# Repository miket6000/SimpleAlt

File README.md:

# SimpleAlt

A simple barometer based peak and logging altimeter for model rocketry with USB C charging and data transfer.  

## Technical details

SimpleAlt uses a Bosch BMP280 to measure the barometric altitude of the altimeter. When recording is started by pressing the button it takes a reference measurement which it calls "ground altitude". This is subtracted from the maximum altitude used in displaying the altitude achieved, however the raw barometric altitude is what is recorded onto the flash.  

The micro controller is an STM32F042, chosen for it's small physical size and built in USB peripheral.  

The flash chip is a Windbond W26Q16 which provides 16Mb (2MB) of recording. The current configuration of 5 bytes per sample (a 1 byte label and 32bit altitude) at 50Hz sample rate (this will probably be reduced to 25Hz in the future) provides a bit over 2hrs of continuous recording.  

The 30mAh battery will last approximately 3-4 hours in idle or recording mode, and about 24 hours in sleep mode, hough work is being done to extend this as the micro controller is not currently achieving the expected current draw. The shutdown mode will last approximately forever, however there is a strange bug in the current hardware revision whereby putting the STNS01 into shutdown mode does not fully succeed until the button is released and pressed again to put a load on the LDO. The cause of this is currently unknown.  

Charging, battery protection and the LDO are all supplied by the STNS01.  

## Using SimpleAlt

SimpleAlt has a simple user interface consisting of a single button and a single green LED (marked 's', for status). This allows it to be as light as possible but may take some getting used to.  

To show how this works this document describes LED flashes between angled brackets <>. A number between the brackets indicates the number of times the LED will flash. A '.' indicates a short pause and a '-' indicates a long pause. e.g.  
< 9 . 10 . 6 - >  
indicates 9 flashes, a short pause, 10 flashes, a short pause and then 6 flashes followed by a long pause. Most flashing sequences will repeat, the exception being the Button mode.  

### The Button
All operations are performed with a single press of the button. To change which options you want you simply hold the button down longer. The options available are:  
1. Wake from Sleep - If the SimpleAlt is in sleep mode, a quick press of the button will wake it up into Idle mode.  
2. Start/Stop recording - A slightly longer press on the button, until you see the first flash on the green LED < 1 >, will start or stop recording.  
3. Enter Sleep mode - holding the button for longer will result in a double flash of the LED after the first flash < 1 . 2 >. Releasing the button now will cause the SimpleAlt to go into sleep mode.  
4. Enter Shutdown mode - holding the button for longer still will result in a triple flash after the double flash < 1 . 2 . 3 >. Releasing the button now will result in the SimpleAlt going into Shutdown mode. The only way to wake SimpleAlt from Shutdown mode is to plug a power supply into the USB connector.  

Thats it! 

### The Green LED

< 1 - >     Idle mode  
< 1 . 2 . > Recording mode  
  
The LED is used to provide status and instant altitude information. Depending on the state of the SimpleAlt it will be displaying one of the below bits of information:
1. Idle mode - a single flash repeating < 1 - >.  
2. Recording mode - the led will alternate between 1 flash and 2 flashes with a short delay between them < 1 . 2 . >.  
3. Button mode - while holding down the button the led will flash once, then twice, then three times to indicate when to release to achieve different functions as described in the button section.  
4. Altitude mode - After exiting recording mode, so long as there was an altitude gain of at least 1m, the led will flash out the maximum altitude in metres. The number of flashes indicates the digit for each place in the number. Leading zero's are not flashed out, and a zero is otherwise flashed out as 10 flashes. So for example if your rocket got to 207m the SimpleAlt will flash < 2 . 10 . 7 - > and then repeat.  

### Charging

Plugging the SimpleAlt into a USB C power supply will result in it charging the battery. While charging the red LED will illuminate. When the battery is full the red LED will turn off. If a fault occured during charging (e.g. the battery voltage never rises high enough) the red LED will flash. This indicates a fault with the hardware or battery and will need to be repaired.  

### Putting it all together

A day flying might look like the following.  

Charge the SimpleAlt by plugging it in. When the red LED turns off, it's charged so unplug it and put it into Sleep mode by holding down the button until you see the double flash.  

Get to the flying field and get set up. When the rocket is ready to launch a quick press on the button wakes up the SimpleAlt and it starts slowly flashing that it's in Idle mode. Holding the button until the first flash puts the SimpleAlt into recording mode (and also sets the ground level), it starts flashing < 1 . 2 . 1 . 2 > put it into the payload bay and launch your rocket.  

On recovery of your rocket press the button until the green LED gives a single flash < 1 > and release to stop recording. The SimpleAlt will now flash out the altitude your rocket achieved in metres.  

Hold the button until the double flash to put the altimeter back into sleep mode, or load it straight into the next rocket and start recording again.  

Back at a computer use the plug the SimpleAlt into your computer using a USB C cable and use the Simple application to download your flights. The flights are added onto the list in order that they occured and the application also gives you the duration of the flight (from starting to stopping the recording) to help you find the right flights to download. For more details see the app guide.

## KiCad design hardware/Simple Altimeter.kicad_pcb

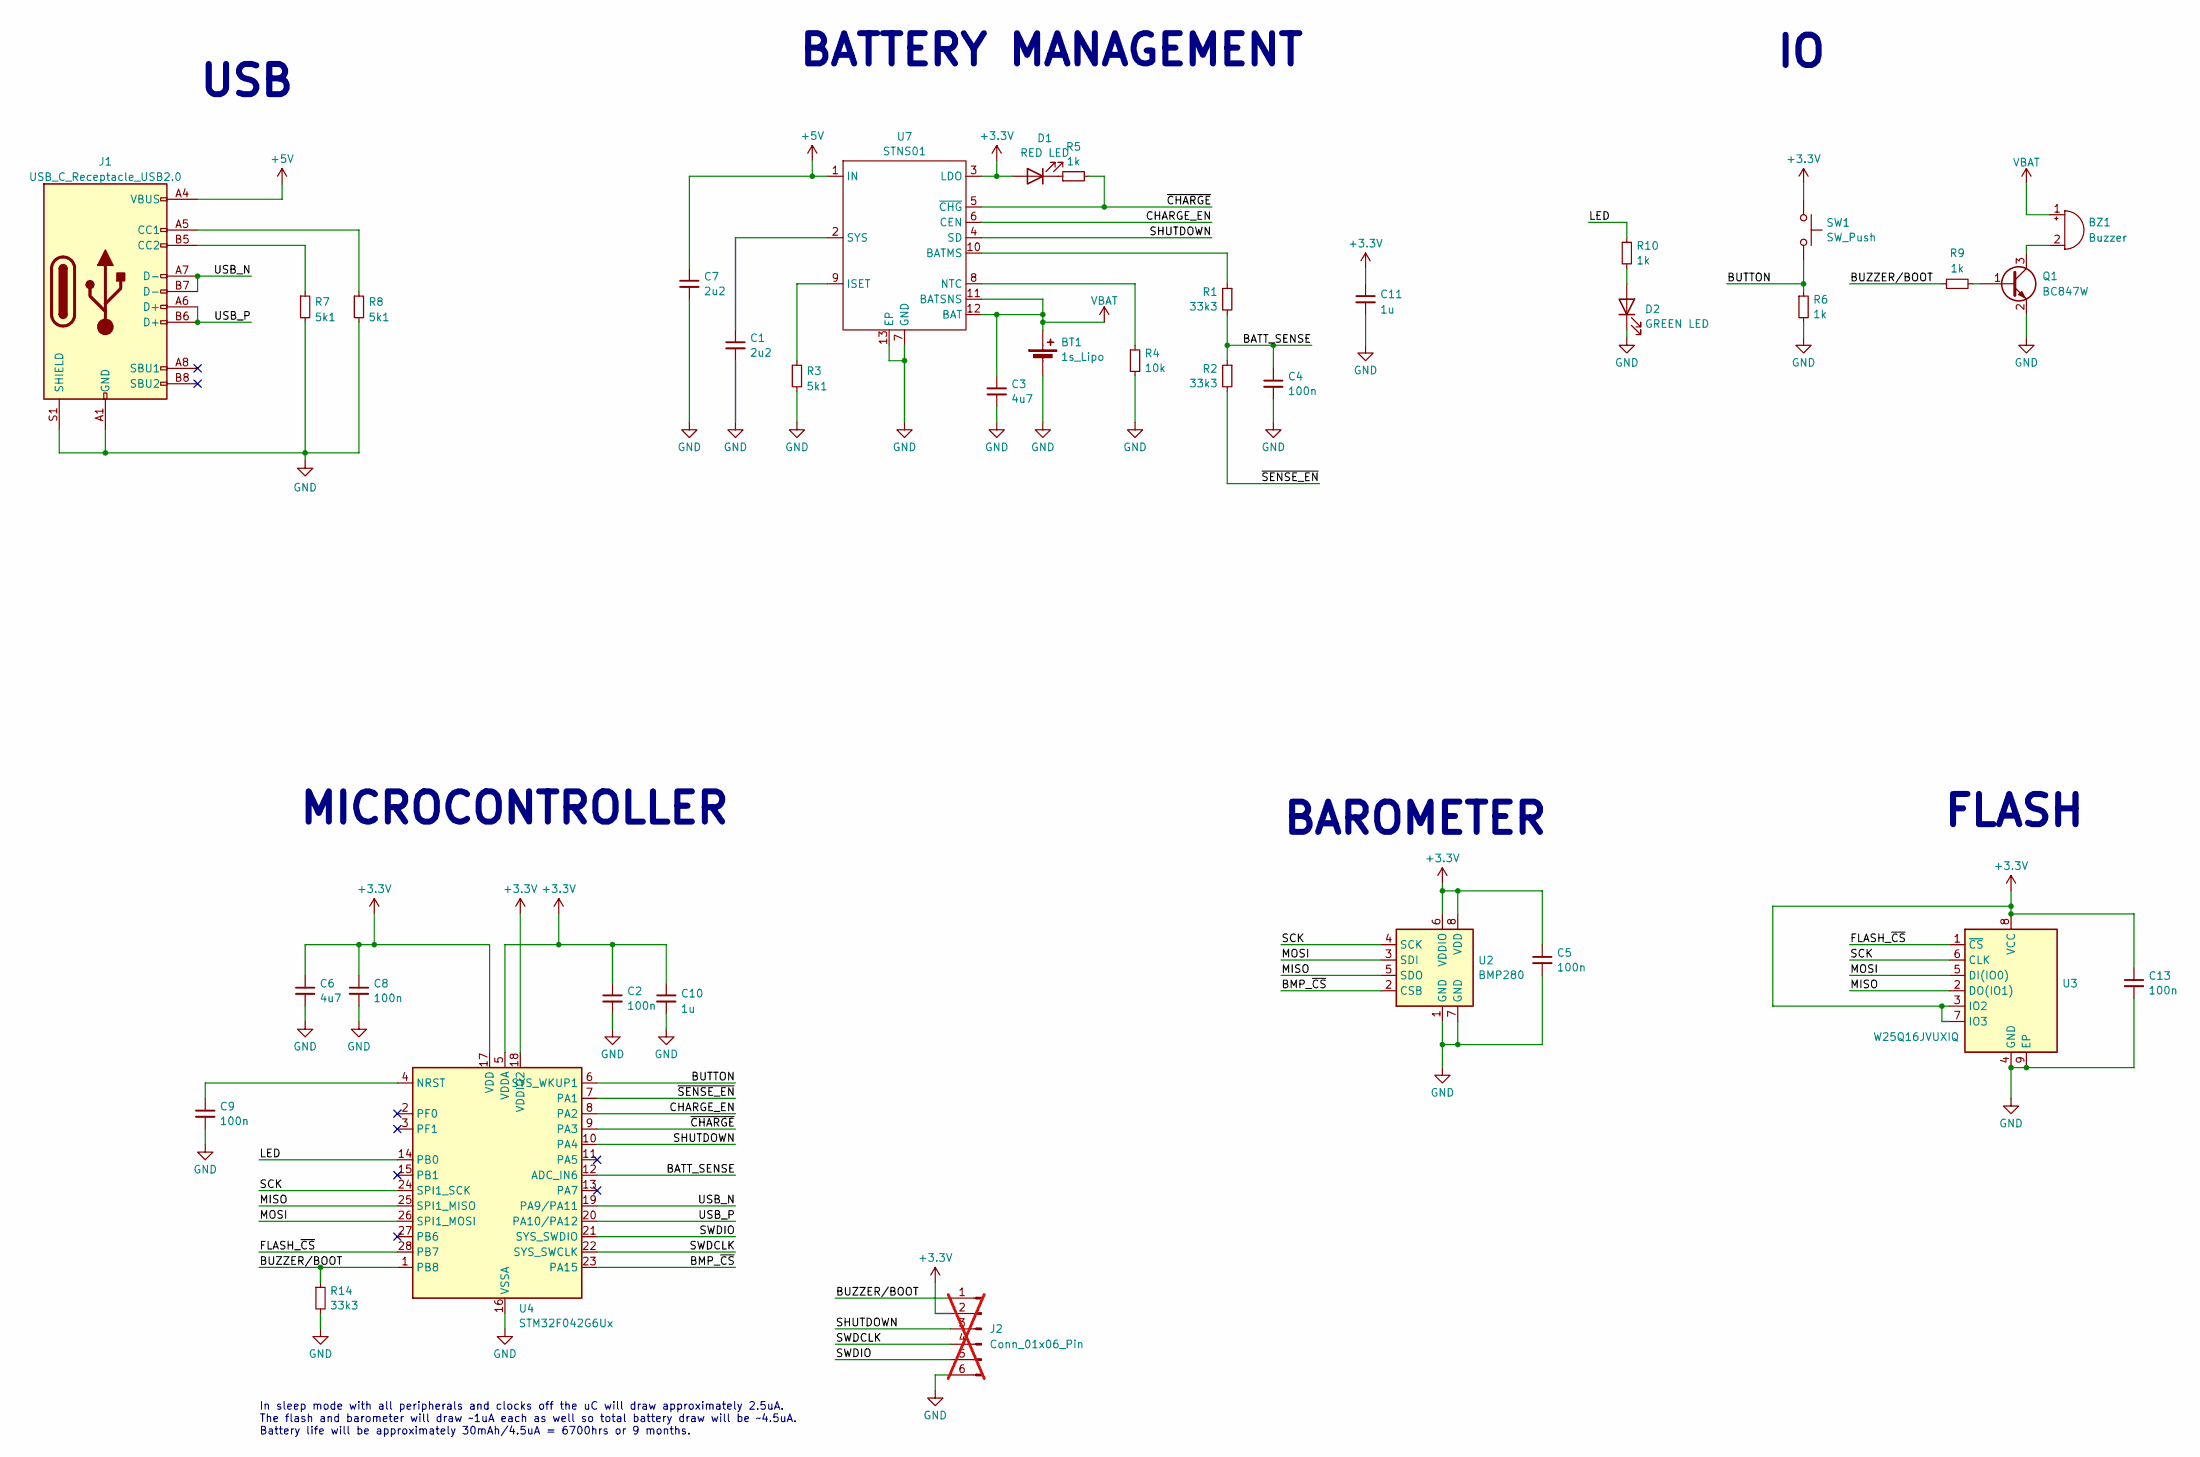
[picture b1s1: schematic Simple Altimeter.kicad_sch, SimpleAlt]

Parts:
BT1: 1s_Lipo; Lipo 401010
BZ1: Buzzer; Buzzer_0502
C1, C7: 2u2; C_0402_1005Metric; JLC Part Number C15849
C2, C4, C5, C8, C9, C13: 100n; C_0402_1005Metric
C3, C6: 4u7; C_0402_1005Metric; JLC Part Number C15849
C10, C11: 1u; C_0402_1005Metric; JLC Part Number C15849
D1: RED LED; LED_0603_1608Metric
D2: GREEN LED; LED_0603_1608Metric
J1: USB_C_Receptacle_USB2.0; USB_C_Receptacle_Palconn_UTC16-G; JLC Part Number C2831450
J2: Conn_01x06_Pin; PinHeader_1x06_P1.27mm_Vertical; not fitted
Q1: BC847W; SOT-323_SC-70
R1, R2, R14: 33k3; R_0402_1005Metric; JLC Part Number C3013567
R3, R7, R8: 5k1; R_0402_1005Metric; JLC Part Number C3013567
R4: 10k; R_0402_1005Metric; JLC Part Number C3013567
R5, R6, R10: 1k; R_0402_1005Metric; JLC Part Number C3013567
R9: 1k; R_0402_1005Metric
SW1: SW_Push; SW_SPST_B3U-1000P
U2: BMP280; Bosch_LGA-8_2x2.5mm_P0.65mm_ClockwisePinNumbering
U3: W25Q16JVUXIQ; Winbond_USON_8_EP_2x3mm
U4: STM32F042G6Ux; QFN-28_4x4mm_P0.5mm
U7: STNS01; DFN-12-1EP_3x3mm_P0.45mm_EP1.65x2.38mm

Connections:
+3.3V: C2.1, C5.1, C6.1, C8.1, C10.1, C11.1, C13.1, D1.2 (A), J2.2, SW1.2, U2.6 (VDDIO), U2.8 (VDD), U3.3 (IO2), U3.7 (IO3), U3.8 (VCC), U4.5 (VDDA), U4.17 (VDD), U4.18 (VDDIO2), U7.3 (LDO)
+5V: C7.1, J1.A4 (VBUS), J1.A9 (VBUS), J1.B4 (VBUS), J1.B9 (VBUS), U7.1 (IN)
/BATT_SENSE: C4.1, R1.2, R2.1, U4.12 (ADC_IN6)
/BMP_~CS: U2.2 (CSB), U4.23 (PA15)
/BUTTON: R6.1, SW1.1, U4.6 (SYS_WKUP1)
/BUZZER/BOOT: J2.1, R9.1, R14.1, U4.1 (PB8)
/CHARGE_EN: U4.8 (PA2), U7.6 (CEN)
/FLASH_~CS: U3.1 (~CS), U4.28 (PB7)
/LED: R10.1, U4.14 (PB0)
/MISO: U2.5 (SDO), U3.2 (DO(IO1)), U4.25 (SPI1_MISO)
/MOSI: U2.3 (SDI), U3.5 (DI(IO0)), U4.26 (SPI1_MOSI)
/SCK: U2.4 (SCK), U3.6 (CLK), U4.24 (SPI1_SCK)
/SHUTDOWN: J2.3, U4.10 (PA4), U7.4 (SD)
/SWDCLK: J2.4, U4.22 (SYS_SWCLK)
/SWDIO: J2.5, U4.21 (SYS_SWDIO)
/USB_N: J1.A7 (D-), J1.B7 (D-), U4.19 (PA9/PA11)
/USB_P: J1.A6 (D+), J1.B6 (D+), U4.20 (PA10/PA12)
/~CHARGE: R5.2, U4.9 (PA3), U7.5 (~CHG)
/~SENSE_EN: R2.2, U4.7 (PA1)
GND: BT1.2 (-), C1.2, C2.2, C3.2, C4.2, C5.2, C6.2, C7.2, C8.2, C9.2, C10.2, C11.2, C13.2, D2.1 (K), J1.A1 (GND), J1.A12 (GND), J1.B1 (GND), J1.B12 (GND), J1.S1 (SHIELD), J2.6, Q1.2 (E), R3.2, R4.2, R6.2, R7.2, R8.2, R14.2, U2.1 (GND), U2.7 (GND), U3.4 (GND), U3.9 (EP), U4.16 (VSSA), U7.7 (GND), U7.13 (EP)
unnamed: BZ1.2 (-), Q1.3 (C)
unnamed: D1.1 (K), R5.1
unnamed: D2.2 (A), R10.2
unnamed: J1.A5 (CC1), R8.1
unnamed: J1.B5 (CC2), R7.1
unnamed: Q1.1 (B), R9.2
unnamed: C9.1, U4.4 (NRST)
unnamed: R1.1, U7.10 (BATMS)
unnamed: R3.1, U7.9 (ISET)
unnamed: R4.1, U7.8 (NTC)
unnamed: C1.1, U7.2 (SYS)
VBAT: BT1.1 (+), BZ1.1 (+), C3.1, U7.11 (BATSNS), U7.12 (BAT)

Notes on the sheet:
FLASH
BAROMETER
MICROCONTROLLER
USB
In sleep mode with all peripherals and clocks off the uC will draw approximately 2.5uA. The flash and barometer will draw ~1uA each as well so total battery draw will be ~4.5uA. Battery life will be approximately 30mAh/4.5uA = 6700hrs or 9 months.
BATTERY MANAGEMENT

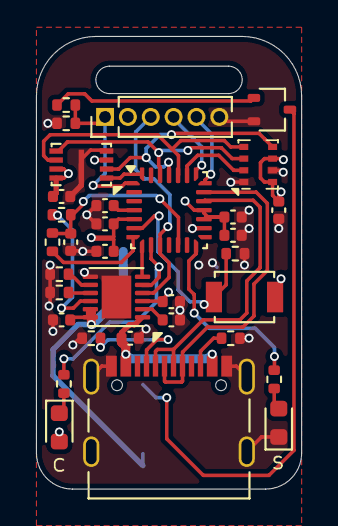
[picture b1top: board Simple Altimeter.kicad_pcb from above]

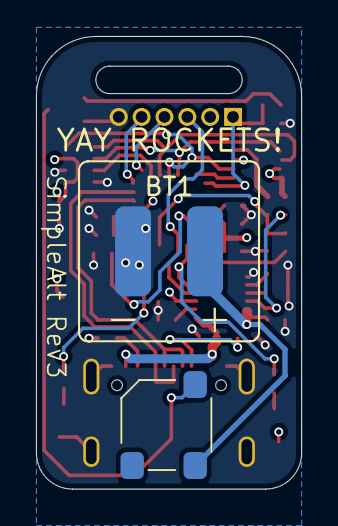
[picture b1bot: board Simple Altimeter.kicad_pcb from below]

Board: 4 copper layers, 14.7 x 25.1 mm, 35 parts (2 on the bottom side), 32 nets.

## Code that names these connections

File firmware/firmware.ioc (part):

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Mcu.Name=STM32F042G(4-6)Ux
Mcu.Package=UFQFPN28
Mcu.UserName=STM32F042G6Ux
PA0.GPIOParameters=GPIO_Label
PA0.GPIO_Label=BUTTON
PA0.Mode=SYS_WakeUp0
PA0.Signal=SYS_WKUP1
PA1.GPIOParameters=PinState,GPIO_Label
PA1.GPIO_Label=nSENSE_EN
PA1.PinState=GPIO_PIN_SET
PA1.Signal=GPIO_Output
PA11.Mode=Device
PA11.Signal=USB_DM
PA12.Mode=Device
PA12.Signal=USB_DP
PA13.Mode=Serial_Wire
PA13.Signal=SYS_SWDIO
PA14.Mode=Serial_Wire
PA14.Signal=SYS_SWCLK
PA15.GPIOParameters=PinState,GPIO_PuPd,GPIO_Label
PA15.GPIO_Label=BMP_CS
PA15.GPIO_PuPd=GPIO_PULLUP
PA15.PinState=GPIO_PIN_SET
PA15.Signal=GPIO_Output
PA2.GPIOParameters=PinState,GPIO_Label
PA2.GPIO_Label=CHARGE_EN
PA2.PinState=GPIO_PIN_SET
PA2.Signal=GPIO_Output
PA3.GPIOParameters=GPIO_PuPd,GPIO_Label
PA3.GPIO_Label=nCHARGE
PA3.GPIO_PuPd=GPIO_PULLUP
PA3.Signal=GPIO_Input
PA4.GPIOParameters=PinState,GPIO_PuPd,GPIO_Label
PA4.GPIO_Label=SHUTDOWN
PA4.GPIO_PuPd=GPIO_PULLDOWN
PA4.PinState=GPIO_PIN_RESET
PA4.Signal=GPIO_Output
PA6.GPIOParameters=GPIO_Label
PA6.GPIO_Label=BATT_SENSE
PA6.Mode=IN6
PA6.Signal=ADC_IN6
PB0.GPIOParameters=PinState,GPIO_Label
PB0.GPIO_Label=LED
PB0.PinState=GPIO_PIN_RESET
PB0.Signal=GPIO_Output
PB3.Mode=Full_Duplex_Master
PB3.Signal=SPI1_SCK
PB4.Mode=Full_Duplex_Master
PB4.Signal=SPI1_MISO
PB5.Mode=Full_Duplex_Master
PB5.Signal=SPI1_MOSI
PB7.GPIOParameters=PinState,GPIO_PuPd,GPIO_Label
PB7.GPIO_Label=FLASH_CS
PB7.GPIO_PuPd=GPIO_PULLUP
PB7.PinState=GPIO_PIN_SET
PB7.Signal=GPIO_Output
RCC.SYSCLKFreq_VALUE=48000000
RCC.SYSCLKSource=RCC_SYSCLKSOURCE_HSI48
board=custom

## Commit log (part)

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2024-06-22 Initial Commit
    Contains draft version of Kicad project files and production outputs. Also includes PDF schematic in docs folder.
2024-06-22 Added 3d render
2024-06-22 Added some of the critical datasheets.
2024-06-22 Fixed boot pin and strengthened teather loop. Added BOMs and manufacturing data.
2024-06-22 Corrected Q1 schematic symbol (was NMOS, now correctly showing PMOS)
2024-06-22 Corrected Q2 part number.
2024-06-22 updated button part number
2024-06-23 Adding operation.md
2024-06-24 Initial commit of STNS01 fork. This will probably become main at some stage in the future.
2024-06-24 Added power off method for debug, and updated operation.md for new hardware. Cleaned up production files.
2024-06-24 fixed footprint for W25Q16JVU
2024-06-26 Adding autogenerated firmware from CubeMX with hardware peripherals configured.
2024-06-26 Updated component 3d models and regenerated render.
2024-07-12 add blinky app with basic power management and button behaviour beware, it's an ugly proof of hardware, not 'real' code.
2024-07-12 Fixed button standby feature. Hold button for >2 seconds to sleep, >5 seconds to shutdown.
2024-07-13 Add a workflow to check compilation.
2024-07-13 Update workflow to use ubuntu
2024-07-13 Ignore build files and add make recipie to program board
2024-07-13 fix white space in Makefile
2024-07-15 Changed USB device from Mass Storage to CDC and added dummy transmitter to main loop. Also added DMA for SPI, not currently configured.
2024-07-16 Added demo of led blink sequence engine functionality. Need to add function to modify blink_queue.
2024-07-16 changed 'queue' to 'sequence' in variable names and added a short pause
2024-07-16 Added capability to define the sequence outside of led.c
2024-07-19 updated LED sequence engine
2024-07-20 Add some makefile targets for setup and debugging
2024-07-20 cleaning up coding convention (moving towards 'C Coding Standard') and moved power management into it's own file.
2024-07-21 Added driver and demo for the bmp280. USB prints out voltage, temperature and pressure.
2024-07-24 Added tool to precalculate pressure to altitude lookup table and implemented function to calculate and report altitude.
2024-07-27 adding test & interative terminal
2024-07-27 added parameter capability to command interpreter and added ground level subtraction capability.
2024-07-28 fixed write enable function in w25q.c added a raw register read function to the command interpreter, and cleaned up some global variables.
2024-07-28 fixed error where a delay in the USB receive routine would cause USB to crash. Fix was to simplify USB receive routine to a single memcpy.
2024-07-28 cleaning up temporary files and provided .gitignore
2024-07-28 basic working flash using w25qxx library.
2024-07-29 working recording to flash by using the button to toggle 'record' mode.
2024-07-29 added simple app to get logs from altimeter and create csv file
2024-07-30 fixed unsigned int error in altitude calculation
2024-07-30 fixed previous fix (didn't remove a function that relied on gruond level function) and improved power on button logic.
2024-07-30 Added binary download of data and updated python app to improve read speeds and actually create the csv file.
2024-07-31 Update simple.py to make altitude signed integer.
2024-07-31 Update simple.py to correct csv line endings
2024-07-31 index on main: d039ded Added binary download of data and updated python app to improve read speeds and actually create the csv file.
2024-07-31 Updated app to allow user to select which of the detected flights to download and added first successful launch plot to docs
2024-07-31 fixed csv titles
2024-08-02 Improvements to shutdown code, increased maximum pressure capability, added led_add_number_sequence() capbility and changed logging to relative altitude instead of absolute.
2024-08-03 Fixed led altitude flashing
2024-08-06 added c version of application
2024-08-06 removed build artifact
2024-08-07 pulled out button code into a seperate file, added a more traditional state machine to main loop and updated button logic to indicate how long to hold the button.
2024-08-07 updated README with technical overview and usage isntructions.
2024-08-07 Update README.md
    Fixed markdown formatting errors.
2024-08-10 made significant improvements to data transfere speed (USB buffer read/write shouldn't have been in the systick gated code)
2024-08-10 Added basic flutter based UI. Only tested on Linux.
2024-08-12 added binary dump to app/c and improved axis title readability in app/flutter.
2024-08-13 fixed state transition from recording to SLEEP or SHUTDOWN causing loss of data.
2024-08-14 Added app screenshot to docs.
2024-08-14 fixed initalization error in idle timeout counter
2024-08-14 updated readme with render and app screenshot
2024-08-14 changed filename for screenshot
2024-08-14 fixed very annoying problem where the flash chip was put to sleep but not woken up on power up, causing issues reading from and writing to it.
2024-08-18 tidied up flutter app, improved chart tooltip and added save capabilities.
2024-08-18 minor refactoring
2024-08-25 added flash dump capability to c app.
2024-08-26 moderate refactor of power and filesystem code to improve modularity
2024-08-26 Added bounds checking to flash writes to prevent overrunning the available flash space and corrupting the filesystem.
2024-08-28 fixed error with serial port not being correctly configured and binary dump reading too many bytes.
2024-08-31 Make C app build on FreeBSD 14.1
2024-08-31 Add C app build to workflow
2024-08-31 Run workflow every push or pull request
2024-08-31 Switch buffers to use void* rather than uint8_t*
    void * is a pointer to anything which is what you probably want here.
    It also avoids the cast when calling but may require casting in the function.
    also trailing white space has been removed.
2024-08-31 Add additional data items to each record.
2024-08-31 Make all warnings treated as errors
2024-09-01 First pass at pulling multiple records out of the flash
2024-09-01 WIP: begin updating the dart to handle multiple records types
2024-09-04 added configuration capability and reduced heap size to 0 to free up RAM
2024-09-04 changed fs_save data type to void *, and added other variables to log.
2024-09-05 Updated timing system to make functions largely tick length agnostic. Added ability to log variables at differnt rates. Improved usability of fs_read_config.
2024-09-09 Updated capabilities to allow logging of multiple variables at varied sample rates and updated c app to be able to read them. Also added capability to include settings (such as sample rates) and reco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
2024-09-09 minor refactoring of c app
2024-09-09 minor refactoring to simple.c
2024-09-11 Cleaned up c app recording.c/h by adding a function to the RecordType that parses the raw data into the correct datatype and increments the data pointer accordingly.
2024-09-14 Changed index labels to lower case and updated c app to read new format.
2024-09-14 Improved usability of local altimeter dump when an altimeter is not connected.:
2024-09-14 tidied up the setting readout in the c app and cached the UID in the altimeter as the readback was occasionally timing out in the c app
2024-09-15 fixed array index off by one error in both recording.c and simple.c
2024-09-18 added dynamic clock scaling to allow lower power in normal modes, but maintain full performance in USB data upload
2024-09-20 Pulled in Nick Lott's changes to add debug option with power off disabled
2024-09-20 changed UID to use stm32 UID rather than flash UID, and modified c app altimeter_get_data to use length rather than end address.
2024-09-22 changed uid to uint32 in app and updated command interpreter callbacks to include a null pointer allowing a lot of the callbacks to be more generic.
2024-09-26 fixed spelling mistake and made SettingType an unnamed struct.
2024-09-26 Added new altimeter and recording dart files in flutter app for review. The home_page has not been updated to use the new interface yet.
2024-09-30 Updated flutter app to plot multiple dataplots.
2024-09-30 updated altimeter to dump all measured parameters when a recording starts, regardless of sample rate. This allows a graphing application to initalize values. Previously unintialized values were consi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
2024-09-30 Made altimeter a singleton class and added a second tab for settings
2024-10-02 Added the ability to specify the colour for records in the record structure as well as to determine whether or not a particular record was plotted. Refactored all the Axis code to make it neater and 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
2024-10-03 Refactored to make data phase correct when pulled off altimeter. This requires reconstructing EVERY tick the altimeter recorded for, regardless of whether anything was recorded. I will need to correc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
2024-10-03 Refactored again to instead record time and value for each recording allowing phase correct reconstruction without introducing an excessive number of redundant data points. This has broken the CSV ex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
2024-10-05 Added a settings page (very basic so far) and updated the AltitudeChart to have proper scaling for nice axis values, and properly controlled and aligned axis titles
2024-10-05 removed initial dump of un-logged parameters.
2024-10-05 Updating settings now takes effect in the graph plot immediately. This is accomplished with global keys which is not perfect, but is effective.
2024-10-06 Fixed bug where the default power off timeout was converted from seconds to ticks twice, and fixed startup code to wait for the button to be released, rather than using a 1 second delay and assuming 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
2024-10-06 Increased minimum power off timeout to 60 seconds. If set shorter it will never auto power off. This makes sure you can't accidentally set a power off so short that you can't change it therefore "bri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
2024-10-06 Added initial settings management sketch.
2024-10-08 Added configuration save capability and functionality to only show 2000 points across the display to speed up application for larger datasets.
2024-10-11 Fixed csv export. Added horizontal zoom to altitude graph and refactored so that axis persist and can be updated, rather than regenerating them on every rebuild.
2024-10-11 minor refactor of getCSV to improve comments and readability
2024-10-12 Added flash remaining and modified layout of settings page to make it dynamic. It's not pretty, and will need more work, mostly just playing with ideas.
2024-10-12 Bug fix where axis (and therefor graph data) weren't updating on Dropdown select. Also corrected flash utilization calculation
2024-10-12 added write retry after finding a noisy USB supply could cause flash write failures.
2024-10-13 minor cleanup and fixed a bug where jumping quickly in zoom could cause graph to extend beyond intended area.
2024-10-13 Removed flash retry which didn't fix issue, instead combined label and value writes into a single buffer and write as a single write
2024-10-17 Refactored altimeter code to add record types and settings as structs and moved time based code into a simple task manager.
2024-10-17 added ability to erase and reset altimeter to the flutter app.
2024-10-17 Minor updates to firmware main.c
    Changed state and usb_connect to use typedef enums rather than #define and changed usb connect functions to disable snooze when connected.
2024-10-18 Added backspace capability to command line interpreter and minor power cleanup in main.c
2024-10-19 Added coloured circle's to settings page to indicate plot colour
2024-10-20 updated status logic and shifted max_alt to be absolute barrometric altitude, rather than above ground level for intermediate calculations
2024-10-20 removed extranious ringbuffer.h include in main.c
2024-10-20 Updated altimeter so settings changes no longer require a restart of the altimeter. This addresses an annoying bug where the app would use different settings for display that were used to generate th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

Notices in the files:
hardware/Simple Altimeter.kicad_pcb:
(C) 2024 Michael Turner
